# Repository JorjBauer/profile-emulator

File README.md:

# ProFile emulator

This is a replacement for an Apple ProFile hard drive. It plugs into the cable
from an Apple ][ ProFile interface card, answers the card the way a real
ProFile does, and serves blocks from disk images on a microSD card.

## How it got here

In 2021 I built a reader for my ProFile 10 around a Teensy 4.1, so I could get
the drive's contents into a disk image. That's
[profile-dumper](https://github.com/JorjBauer/profile-dumper), and the build
log is on [Hackaday](https://hackaday.io/project/179930-apple-profile-10mb-hard-drive-reader).

At the same time, I hand-wired a second Teensy board meant to turn that around
and pretend to be the drive instead of the host. Its code wasn't finished
until 2026. That's the Teensy version in `teensy/`, and it works on my //e.
But it's at the limit of what the Teensy can do, and it took some clever
optimization to get there.

So I moved it to an FPGA. I chose to make it FPGA-only, with no
microcontroller, to keep the cost down. That drove the complexity up. I started
on an Alchitry Cu (iCE40 HX), moved to the Alchitry Au (Artix-7) when the
iCE40's carry chains became the bottleneck, and then moved to a ULX3S-12F
(ECP5). If you find comments about the iCE40 or the Artix-7, that's why.

Then I built two boards of my own around the same ECP5 in a TQFP-144. r1
worked after some rework, but it had the wrong footprint for the flash chip,
along with other mistakes. r2 fixed them, and it's been serving my //e since
2026-10-23.

All of my testing is on a //e with a ProFile card whose ROM is 341-0299-B. I
haven't tried an Apple ///.

## What's here

- `fpga/`: the current design. Its `README.md` is the technical notebook:
  architecture, the serial report, the boot menu, and the tests.
  - `src/` and `sim/`: the Verilog and its testbenches.
  - `constraints/`: pinouts for the ULX3S (`ulx3s.lpf`) and r2
    (`profile-drive-r2.lpf`).
  - `tools/`: node scripts. One imports the selector's blobs into the build;
    the others check a card image against what the drive serves.
  - `carrier/ULX3S-ADAPTER.md`: wiring the interface board to a ULX3S.
  - `hw-r2/profile-drive/`: the r2 board. The KiCad project, the Gerber and
    stencil zips, a placement sheet and an assembly drawing.
  - `hw-r2/BRINGUP-r2.md`: building an r2 board and bringing it up.
  - `hw-r2/enclosure/`: a printed case shaped like a tiny ProFile.
- `teensy/`: the Teensy 4.1 version. It still works.
- `selector/`: a submodule with the 6502 boot menu that both versions serve,
  so you can pick an image from the //e.

The ProFile protocol, the DB-25 pinout and the interface card's behavior are
documented in profile-dumper's `PROTOCOL.md` and `HARDWARE.md`. The READMEs
here refer to them often.

## Getting the code

The selector is a submodule, so clone with it:

    git clone --recursive <this repo>

If you already cloned without it, run `git submodule update --init`.

## Where to start

### Preparing an SD card

Format it FAT32, put your images in a directory named `HD`, and create
`/profile.cfg` by hand with any non-empty content. The drive can rewrite
files, but it can't create them. The details are in `fpga/README.md` under
"Preparing the SD card".

### Building for a ULX3S

You need [oss-cad-suite](https://github.com/YosysHQ/oss-cad-suite-build),
which has yosys, nextpnr-ecp5, ecppack, iverilog, openFPGALoader and fujprog.
You also need `node`, because the build uses it to import the selector's
blobs. Then, in `fpga/`:

    make sim-all    run the testbenches
    make            build the bitstream
    make prog       load it into SRAM, volatile
    make flash      write it to the SPI flash

`make sim-all` stops at the first bench that fails. `fpga/README.md` has the
full list of targets.

The ULX3S needs an interface board between it and the DB-25: two 74LVC245s
that shift the 5V bus down to 3.3V. Mine was hand-wired on perfboard, and its
design isn't in this repo. `fpga/carrier/ULX3S-ADAPTER.md` has the pin map
from that board to the ULX3S, and the wiring mistakes that damage parts.

### Ordering r2 boards

Everything is in `fpga/hw-r2/profile-drive/`.

- `profile-drive-r2-gerbers.zip` is the board: 4 layers, 1.6 mm, lead-free
  HASL, 1 oz outer copper, 100 x 55 mm.
- `profile-drive-r2-stencil-reduced.zip` is a top paste layer with the
  apertures on U1 and J1 shrunk by 0.04 mm. The full-size paste in the Gerber
  zip bridged their fine-pitch pins on my board. I ordered it in 4 mil
  stainless.
- Every part is on the top side.
- The silkscreen labels are 0.8 mm tall. That's below JLCPCB's standard 1.0 mm
  minimum, and at their limit for high-precision silkscreen (0.8 mm text with
  a 0.1 mm stroke), so ask for high-precision if you want the smallest labels
  crisp.

If you want JLCPCB to assemble it, upload these two as well:

- `profile-drive-r2-bom-jlcpcb.csv`: the BOM, with the manufacturer part and
  the LCSC number for each line. Every LCSC number is the exact part in the
  schematic, except for the LEDs, which the schematic doesn't name. The BOM
  uses red ones (KENTO KT-0603R).
- `profile-drive-r2-cpl-jlcpcb.csv`: the pick-and-place file, in the same
  coordinates as the Gerbers. I haven't had JLCPCB assemble one, so check
  every part's rotation in their preview before you pay. The TQFP, the
  SOT-23s, the TSSOPs and the connectors are the usual suspects.

J4, J5, J6, J7 and SW1 are optional and left out of both files. They're for
programming, debugging and service, and you can solder them on later. A new
board's flash is blank, though, so something has to reach J4's pads once to
load it. I use a pogo-pin clip on J4. A 1x6 header soldered there works too.

As of 2026-10-24, three parts had no stock at JLCPCB: U1 (the FPGA), J1 (the
USB-C socket) and J2 (the DB-25). You'll probably have to send those in
yourself or solder them by hand. R31 (84.5k) had only 17 in stock.

The LCSC numbers are also in the schematic, as an `LCSC` field on each part,
and J4, J5, J6, J7 and SW1 are marked DNP in both the schematic and the board. If
you change the design, KiCad's own BOM and position exports pick both up, but
the two CSV files here won't follow on their own.

### The LEDs

The schematic gives each of the eight LEDs a 1k resistor (R35 to R42, in
order for D1 to D8) and doesn't name a color. That's sized for ordinary red or
yellow 0603 LEDs. The BOM uses red (KENTO KT-0603R, LCSC C2286). For yellow,
NationStar NCD0603Y2 (LCSC C89811) works the same way.

The LEDs and their resistors are optional. Nothing else is on those nets, so
leaving them off only loses the status display and the error codes.

If you use white, blue or true green LEDs, change their resistors to 330R.
Those colors need about 3 V to light, which leaves only a few tenths of a volt
across the resistor from a 3.3 V pin, so at 1k they're dim. On my board D1 to
D4 matter most, so D1 is white, D2 is blue, D3 and D4 are emerald, and R35 to
R38 are 330R.

### Building one by hand

`placement-r2.png` is the assembly sheet. It shows where each part
goes, marks pin 1 (and each LED's cathode) in red, and has a checklist BOM with
quantities and part numbers. `assembly-r2.pdf` puts the values on the
footprints. Use the reduced stencil.

`fpga/hw-r2/BRINGUP-r2.md` walks through the rest: paste and reflow,
inspection, checking the power rails, first power, and programming.

### Updating an r2 board

The flash holds two copies of the gateware: the one that runs, and a golden
copy the board falls back to if the first is ever damaged. A new board gets
both over JTAG, once. After that, an update can come from the SD card.

In `fpga/`, `make r2-flash-dual` builds the gateware and writes both copies,
plus the record that points the FPGA at the golden one. The programmer is an
FT4232H module on J4, through a pogo-pin clip or a header soldered there. The
wiring is in `fpga/README.md` under "Building for the r2 board". Power the
board from USB-C, not from J4. (`make r2-prog` loads SRAM instead, for
testing.)

For an update from the SD card, `make r2-update` builds `R2UPDATE.BIN`. Copy
it to the root of the card and power the board up. It waits until the drive
is idle, so it never slows a boot. If the file holds a newer build than the
one running, the LEDs fill up twice (once checking the file, once writing
it) while the drive keeps serving. After five seconds with no activity from
the //e, the board reboots into the new build. The file can stay on the
card; it's skipped once it's the build that's running, and an older file is
always skipped. Going back to an older build takes JTAG. `fpga/README.md`
has the details under "Updating from the SD card".

To check which build a board is running, hold open-apple while the //e
boots, and the image menu comes up. Row 2 shows the build ID and which copy
it was loaded from, such as `BUILD 80068B67 (PRIMARY)`. Build IDs only go
up, so a higher one is newer. It says `GOLDEN` if the first copy was damaged
and the board fell back. The bottom row shows what each copy in the flash
holds, which only differs from row 2 when an update is waiting for its
reboot. (The menu needs at least one image on the card.)

There are no prebuilt bitstreams yet, so you need the same tools as the ULX3S
build.

### The Teensy version

`teensy/README.md` covers the wiring, the arduino-cli build and the serial
commands. The board was hand-wired, so its README is an as-built description,
not a schematic.

## What doesn't work yet

- The SD card update passes its simulations, but I haven't tried it on a
  board yet. Neither the fallback to the golden copy nor the reboot at the
  end has been seen working on real hardware. JTAG works.
- No prebuilt bitstreams.
- The ULX3S interface board's design isn't published.
- Nobody has tried it on an Apple ///.

## License

MIT. See `LICENSE`.

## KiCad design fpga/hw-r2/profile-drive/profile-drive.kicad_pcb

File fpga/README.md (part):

# ProFile emulator in an FPGA

This is the FPGA version of the drive. It answers the ProFile's DB-25
protocol and serves blocks from an SD card, on a ULX3S or on the r2 board in
`hw-r2/`. The top-level README has the backstory and says where to start; this
is the technical notebook.

`PROTOCOL.md` and `HARDWARE.md` below are the ones in
[profile-dumper](https://github.com/JorjBauer/profile-dumper).

## Preparing the SD card: a file you have to create yourself

Format the card FAT32, put your images in a directory called `HD`, and
then **create `/profile.cfg` in the root of the card by hand**, with
any text editor and any non-zero-length content, so the drive can
remember its state.

**This drive can modify files, but it cannot create them.** Every
write it performs must be in a sector that is already allocated: a
host's write goes into the image's own cluster chain, and remembering
a menu selection rewrites `profile.cfg`'s existing data sector and
then corrects the size in its directory entry. There is no allocator,
no free-cluster search and no FAT writing anywhere in it, because
serving a fixed-size volume never needs one. Only creating a file
would need them. A text file you drop on the card
avoids all that complexity.

The images must be in a directory named `HD` as a practical matter;
the more stuff the descender has to enumerate, the longer it takes for
this device to boot. We have about 0.58s before the Apple ][ ProFile card
ROM gives up; unlike some other cards, it makes one STATUS request and then
bails if it doesn't respond.

## Building it

This builds with an open source toolchain: yosys, nextpnr-ecp5, and
prjtrellis, all of which are part of oss-cad-suite. The build also needs
`node`, which imports the selector's blobs. Source oss-cad-suite's
environment first (`source <wherever you unpacked it>/environment`) and then

    make            synthesize, place and route, pack
    make sim-all    the testbenches. Run these before touching hardware
    make prog       load into SRAM over USB, volatile
    make flash      write SPI flash, survives a power cycle
    make reload     re-load the last SRAM build with no rebuild
    make stat       resource count only: yosys alone, no place and route
    make clean

`make stat` needs nothing but yosys, which makes it the fastest way to see
whether a change still fits.

**SRAM and flash get different bitstreams.** The flash copy is
compressed and configured for fast-read at 38.8 MHz (62 MHz on r2). An
uncompressed stream takes about 2.25 s to load and loses the power-on
race against the //e. Compressed, the same load is about 70 ms.
Loading that same compressed flavor into SRAM over JTAG makes the
ECP5's config engine abort with `BSE Abort ERR` and leaves the device
blank. `make prog` therefore builds and loads the uncompressed
`_nextflash.bit`, and `make flash` the compressed one. Both work via
`fujprog`.

There is one more ECP5 wrinkle worth knowing: this is built as an
ECP5-25F, but I'm using an ECP5-12F to serve it. They're the same
silicon; the 12F has artificial limits that the open source toolchain
is happy to ignore.

Four separate diagnostic bitstreams build from the same sources, each
of which takes the SD engine or the bus for itself and so cannot
coexist with serving a host: `make verify-prog` (whole-volume
checksums), `make dump-prog DLBA=n` (one sector as hex), `make
exercise-prog` (a known pattern on the DB-25 with no host) and `make
stream-prog SBLOCK=n` (a real block onto the DB-25 with no host). Each
is described in its own section below.

### Building for the r2 board

The r2 board in `hw-r2/` is this same design on an LFE5U-12F in a
TQFP-144, with its own pinout in `constraints/profile-drive-r2.lpf`. r2 has
three pins the ULX3S build doesn't, so its top module is `src/top_r2.v`,
which wraps `top` and leaves every other build alone:

- **U3_OE_N** (pin 76) enables U3, the buffer for the host's control lines.
  R53 holds it off until the FPGA is configured, and the gateware ties it low.
  If it isn't driven low, the FPGA never sees /PCMD or /PSTRB.
- **XCVR_OE_N** (pin 74) is held off until the host asserts /PCMD the first
  time, because PD0 to PD7 have no pulls and float with no cable.
- **FPGA_REBOOT** (pin 67) goes to PROGRAMN through R48. The SD update pulls
  it low through an explicit open-drain pad when it's done, and otherwise it's
  released. Don't make it an output assigned `1'bz`: nextpnr turns that into a
  driven pin, and low there reboots the part over and over. It must never be
  driven high either.
- **The flash** (pins 46, 47 and 49, and the configuration clock through
  `USRMCLK`) is ours once the part is configured. The SD update uses it.

It builds next to the ULX3S flavor under its own name:

    make r2             both bitstreams
    make r2-prog        load SRAM over JTAG, volatile
    make r2-reload      the same with no rebuild
    make r2-flash-dual  write both flash images and the jump record over JTAG
    make r2-flash       rewrite just the primary image over JTAG
    make r2-update      build R2UPDATE.BIN, for an update from the SD card

JTAG is an FT4232H module on J4, channel A, under the module's UART
labels: TXD to TCK (J4 pin 4), RXD to TDI (pin 3), RTS to TDO (pin 2),
CTS to TMS (pin 5), GND to pin 6, nothing on pin 1. `R2CABLE=` overrides
the cable name. Power the board from USB-C, not from J4.

After any rebuild, read the catalog back (the dumper's `K`, or a window
read of `$FFFF80`) rather than trusting the boot alone. A build can meet
timing and pass every simulation and still serve a wrong catalog (see the
fat32 note under "Known bring-up items").

The first r2 build lost the power-on race on a
cold start. The //e's card ROM looks for the drive about 0.6 s after
autostart reaches the slot, and if /PBSY or PCHK is wrong it skips the slot
and never asks again. Two things changed, both only for r2:

- The FPGA reads its flash at 62 MHz (`FLASHFREQ`, ecppack's top rate)
  instead of 38.8. The 348 KB compressed load drops from about 72 ms to
  about 45. The W25Q128 is good to 133 MHz.
- The SD card initializes at 397 kHz (`SD_DIV_INIT` 62) instead of 100 kHz.
  That's just under the 400 kHz the SD spec allows for initialization, and
  it's fine now that the socket is on the board rather than on flying leads.
  The first read also happens at this rate, so it's faster too.

After that, reads and writes both run at 8.33 MHz. The ULX3S harness kept
writes at 391 kHz, but the first r2 board passed every rate up to 25 MHz
(see "Measuring an r2 board's SD clock ceilings"), so r2 writes at the read
rate. 8.33 MHz is a third of what the board was shown to do.

The FAT32 directory recursion is still on. It costs boot time when the card
holds a lot of files, which is why the images belong in `HD`.

With both changes, build 10231827 (60.17 MHz against the 50 MHz target)
serves the //e from a cold start. I couldn't measure how much margin is
left. The //e's monitor takes longer to come up than the drive does, so
there's nothing to time on the screen.

## Updating from the SD card

r2 can rewrite its own flash from a file on the SD card and reboot into it.
`src/fw_update.v` does the work, through `src/spi_flash.v`. It's only built
into r2 (`UPDATE_ENABLE`), since the ULX3S has no line from the FPGA to
PROGRAMN.

### The flash layout

    0x000000   the primary image: 256 bytes of $FF, then the bitstream
    0x100000   the golden image, laid out the same way
    0xFFFF00   a jump record pointing at the golden image

The updater only ever writes below 0x100000. If the primary fails to
configure, because an update lost power partway through for instance, the
ECP5 follows the jump record to the golden copy at power-up (Lattice
FPGA-TN-02203). The golden copy carries the updater too, so it finds the file
again and finishes the job. `make r2-flash-dual` writes all three pieces over
JTAG, which a board needs once.

The layout is ecpmulti's, but we don't use ecpmulti. It re-serializes every
bitstream and drops `--compress`, `--freq` and `--spimode`, and r2 needs all
three to win the power-on race. `ecppack --bootaddr` sets multiboot instead,
and `tools/mkupdate.js` writes the jump record. Both images point their next
boot at 0. ecpmulti points the primary at the golden copy instead, and then
the reboot after an update would land on the golden copy, which would write
the same file again and reboot again, forever.

### The file

`make r2-update` builds `R2UPDATE.BIN`: a 512-byte header, then the primary
image padded to whole sectors. The header holds `PEFW`, the board (`R2`), the
payload's length, its CRC-32 and its `BUILD_ID`. Put it in the root of the
card.

### Which build is where

There's no separate version number. The `BUILD_ID` does the job: it's the
minutes since 2026-01-01 00:00 UTC with the top bit set, so it only goes up,
and a higher one is always a newer build. The build puts it in the gateware
and in the bitstream's header as a comment, `PEV:<BUILD_ID>`, ahead of
nextpnr's own. The header comes right after a slot's 256 bytes of $FF, so the
comment always starts 258 bytes into the slot.

At reset, before anything else, the updater reads both slots' headers. That
takes about 30 microseconds and doesn't touch the SD card. Whichever slot
carries the running `BUILD_ID` is the one we were loaded from. If neither
does, the gateware came in over JTAG. A slot can also read `EMPTY` (erased),
or `UNKNOWN` (no build ID in its header). Headers written by builds from
before this change say `PEV:<BUILD_ID>:1.0`, and the updater reads the build
ID out of those too. After an update writes the primary, it reads the
primary's header again, so the menu shows what's waiting for the reboot.

The select menu shows all of it, from the info block (`selector/SELECTOR.md`
has the layout):

    BUILD 80068B67 (PRIMARY)            row 2: what's running, and its slot
    PRIMARY 80068B67  GOLDEN 80068B38   bottom row: what each slot holds

The ULX3S shows only the first line, without a slot. The Teensy shows neither.

Whether the primary matches is all the slot test checks. If the primary's
header survives but the rest of it is damaged, the ECP5 loads the golden
copy instead, and if the two copies are the same build, the menu still says
`PRIMARY`. In that case it's the same gateware either way.

### What happens at power-up

Boot time comes first, so the updater does nothing until the drive is idle:
a full second with no host command, no block reads or writes, and the SD
card at rest. A booting //e reads with gaps of a few milliseconds, so the
updater never touches the card during a boot. Then it looks for
`R2UPDATE.BIN` in the root, which takes a few sector reads. It stops there
if:

- there's no file
- the file's `BUILD_ID` isn't newer than the one that's running. That's
  what keeps an update from repeating, so the file can stay on the card, and
  it means an older file is ignored. Going back to an older build takes
  JTAG (`make r2-flash-dual`).

Otherwise it makes two passes, in the background. The drive keeps serving
the whole time: the updater is the SD card's lowest-priority user, so a host
read waits at most for the one updater read already in flight (well under a
millisecond). The first pass reads the whole file and checks its CRC, and
writes nothing. The second erases each 64 KB block as it reaches it,
programs each sector, and reads it back. An update of the current 371 KB
image reads the card twice and writes about 6 blocks, which takes a few
seconds.

Then it waits for the drive to be idle again, and to stay idle for four
more seconds (five in all), before it pulls PROGRAMN. That reboot is the
only part a host can notice: the drive is gone while the FPGA configures and
mounts the card again, the same wait as at power-up. If the //e is in the middle of something
then, it gets an error. If the host never goes quiet for five seconds, the
board keeps running the old image, and the new one starts at the next
power-up.

The LEDs show it. During the first pass they fill from D1 to D8, blinking.
During the second they fill again, solid. All eight stay lit while it waits
to reboot. A failure blinks D8 and shows the error code on D1 to D4 (D1 is bit
0), until a host appears:

| code | meaning |
|-----:|---------|
| 1 | an SD read failed |
| 2 | the header isn't `PEFW`, or its length is bad |
| 3 | the file is for another board |
| 4 | the payload doesn't match its CRC |
| 5 | the file ends before its payload does |
| 6 | the flash didn't answer as a W25Q128 |
| 7 | an erase timed out |
| 8 | a page program timed out |
| 9 | a sector read back differently |

Errors 2 to 6 happen before anything is written, and so can error 1. Errors 7 to 9, and an error 1 during
the second pass, leave the primary half written. The running image is
fine until power is removed, and at the next power-up the board falls back
to the golden copy, which tries again.

The serial report carries the same status in the `FAT` line, words 4 to 6,
when the self-test's FAT scan isn't built in: `[25:24]` the pass (1 check, 2
write, 3 done), `[19:16]` the error, `[15:0]` the sectors done; then the
sectors in all; then the file's `BUILD_ID`.

`make sim-fw-update` runs it against a hand-built FAT32 card and a model
flash. A good file is written and read back, with its directory entry and
its clusters both scattered so the FAT has to be followed. A file that's
already running, corrupted, built for another board, missing, or that reads
back wrong is refused. Nothing at or above the golden image is ever written.
It doesn't start until the drive is idle, and host activity holds the reboot
off until the drive has been idle long enough.

**None of this has run on a board yet.** The simulation covers the updater's
own logic. It can't show that the ECP5 really falls back to the golden copy,
that `USRMCLK` drives the flash clock as expected, or that the reboot works.
Before trusting it, flash a board with `make r2-flash-dual`, then try an
update. Then erase the first block of the flash over JTAG and power-cycle the
board, to check it comes up from the golden copy.

One case can still loop. If a file passes every check but its image won't
configure, the board falls back to the golden copy, which writes the same
file again, and reboots into it. Each round takes a few seconds, and the
LEDs show it happening. Taking the card out stops it.

## Electrical: the bus is 5V, the FPGA is not

Two 74LVC245s serve as voltage level converters, since the FPGAs are
not 5v tolerant and the ProFile bus is 5V TTL.

## Architecture

    db25 <-> 74LVC245 pair <-> profile_bus (tri-state, parity)
                                    |
                              profile_target      the three-phase protocol FSM
                                    |
                        +-----------+-----------+
                        |                       |
                  block_router            status/geometry
                  (normal blocks,        (spare table for $FFFFFF,
                   $FFFFFE RAM buf,       4 status bytes, the
                   selector magic)        multiple-of-4 rule)
                        |
                +-------+-------+
                |               |
             fat32           selector      the image menu's drive half
        (MBR, BPB, the      ($FFFF00..
         directory walk,     $FFFFFD)
         cluster chains,
         profile.cfg)
                |
             sd_spi  ->  SD card  (SPI mode, CMD17/CMD24)

`reporter` streams the whole diagnostic state out the serial port (the
ULX3S's USB serial, or J5 on r2); it is not in the data path.

Module by module:

- **`profile_bus`** owns the pins: tri-state control, the `DIR`//`OE` pair for
  the translators, and odd parity. Parity is generated for **host-driven bytes
  too**, including the ack (`PROTOCOL.md` §9.4): the drive owns that line in
  both directions. Getting it wrong is what makes a parity latch appear to set
  itself.
- **`profile_target`** implements command / confirmation / data phases, the six
  command bytes, the `$55` ack and the `$AA` NAK, and the //e's two departures
  from the spec: a read is 4 status + 512 with the host then abandoning by
  re-asserting `/PCMD`, and a write is 512 + a 6-byte trailer
  (`PROTOCOL.md` §3 and §9.1, §9.3).
- **`block_router`** decodes the 24-bit block number: normal blocks to the SD
  reader, `$FFFFFE` to the RAM buffer, `$FFFFFF` to the synthesized spare table,
  and the `$FFFF00-$FFFFFD` selector window.
- **`sd_spi`** is a plain SPI block reader: init at 100 kHz (397 kHz on r2),
  run at the measured rates in the table below, CMD17 single-block read and CMD24 write. **Both
  card generations work.** SDHC addresses by block; a card that rejects CMD8 is
  treated as v1, ACMD41 goes out without HCS, CCS comes from the OCR, and CMD17
  arguments are scaled by 512. `make sim-v1` and `make sim-v1skew` are that
  path. It also recovers byte alignment when a card's replies arrive out of
  phase, which the real one does: `make sim-sweep` checks the recovery over all
  eight bit phases.

## Geometry, and what reverse engineering revealed

The claimed volume size in the spare table **must be a multiple of 4**
or the //e's ROM never hands off to the boot block (`PROTOCOL.md`
§9.2). The drive rounds down and caps the claim at `$FFFC`, which is
what the Teensy firmware does, and it will not be configured
otherwise. It is one comparator and it prevents an entire class of "it
reads fine but will not boot". Also see "Geometry: two block counts,
not one" below.

## Testing against the //e, not just the reader

`make sim` runs the protocol against a model of the READER's host
sequence, which is deliberately forgiving: microseconds per byte, a
settling delay after `PR/-W` rises, generous strobes. A drive that
fails there cannot possibly work. Passing it shows very little, and
PROTOCOL.md section 3 says so: the Apple /// and Lisa hosts insert
a delay before their first strobe, "which is why a slow drive works
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
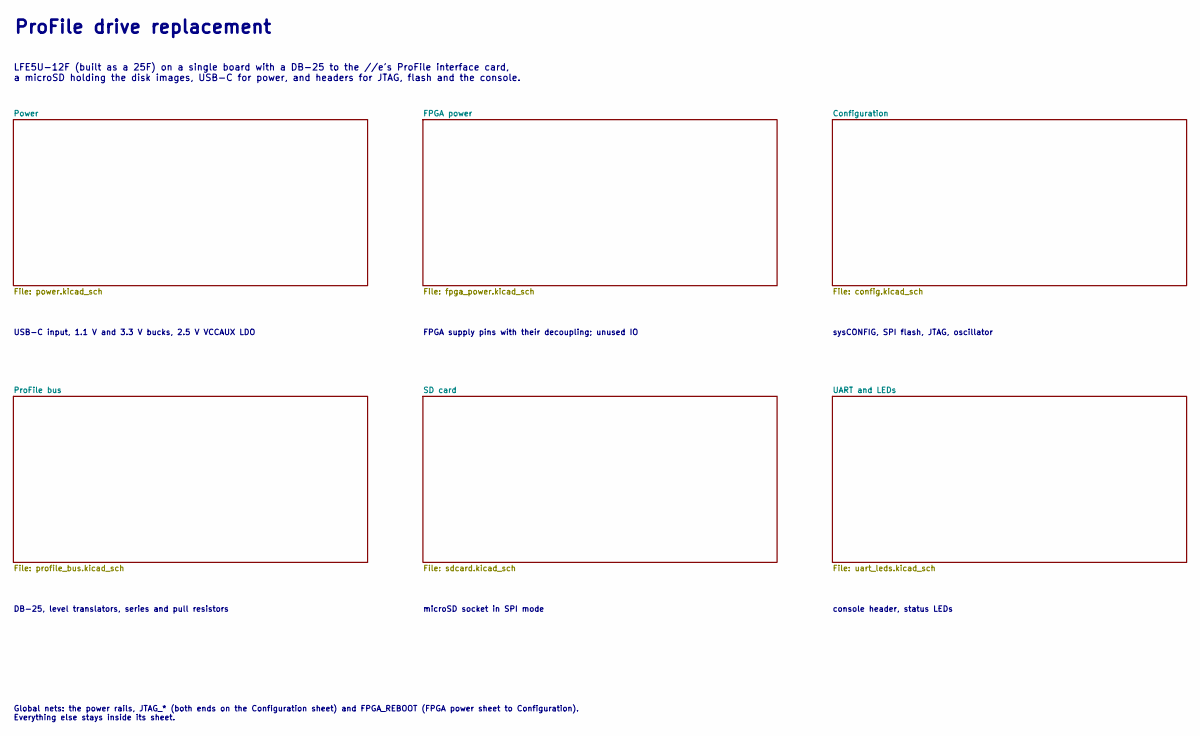
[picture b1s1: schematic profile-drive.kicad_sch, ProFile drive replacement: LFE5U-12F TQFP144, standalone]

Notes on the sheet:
ProFile drive replacement
LFE5U-12F (built as a 25F) on a single board with a DB-25 to the //e's ProFile interface card, a microSD holding the disk images, USB-C for power, and headers for JTAG, flash and the console.
USB-C input, 1.1 V and 3.3 V bucks, 2.5 V VCCAUX LDO
FPGA supply pins with their decoupling; unused IO
sysCONFIG, SPI flash, JTAG, oscillator
DB-25, level translators, series and pull resistors
microSD socket in SPI mode
console header, status LEDs
Global nets: the power rails, JTAG_* (both ends on the Configuration sheet) and FPGA_REBOOT (FPGA power sheet to Configuration). Everything else stays inside its sheet.

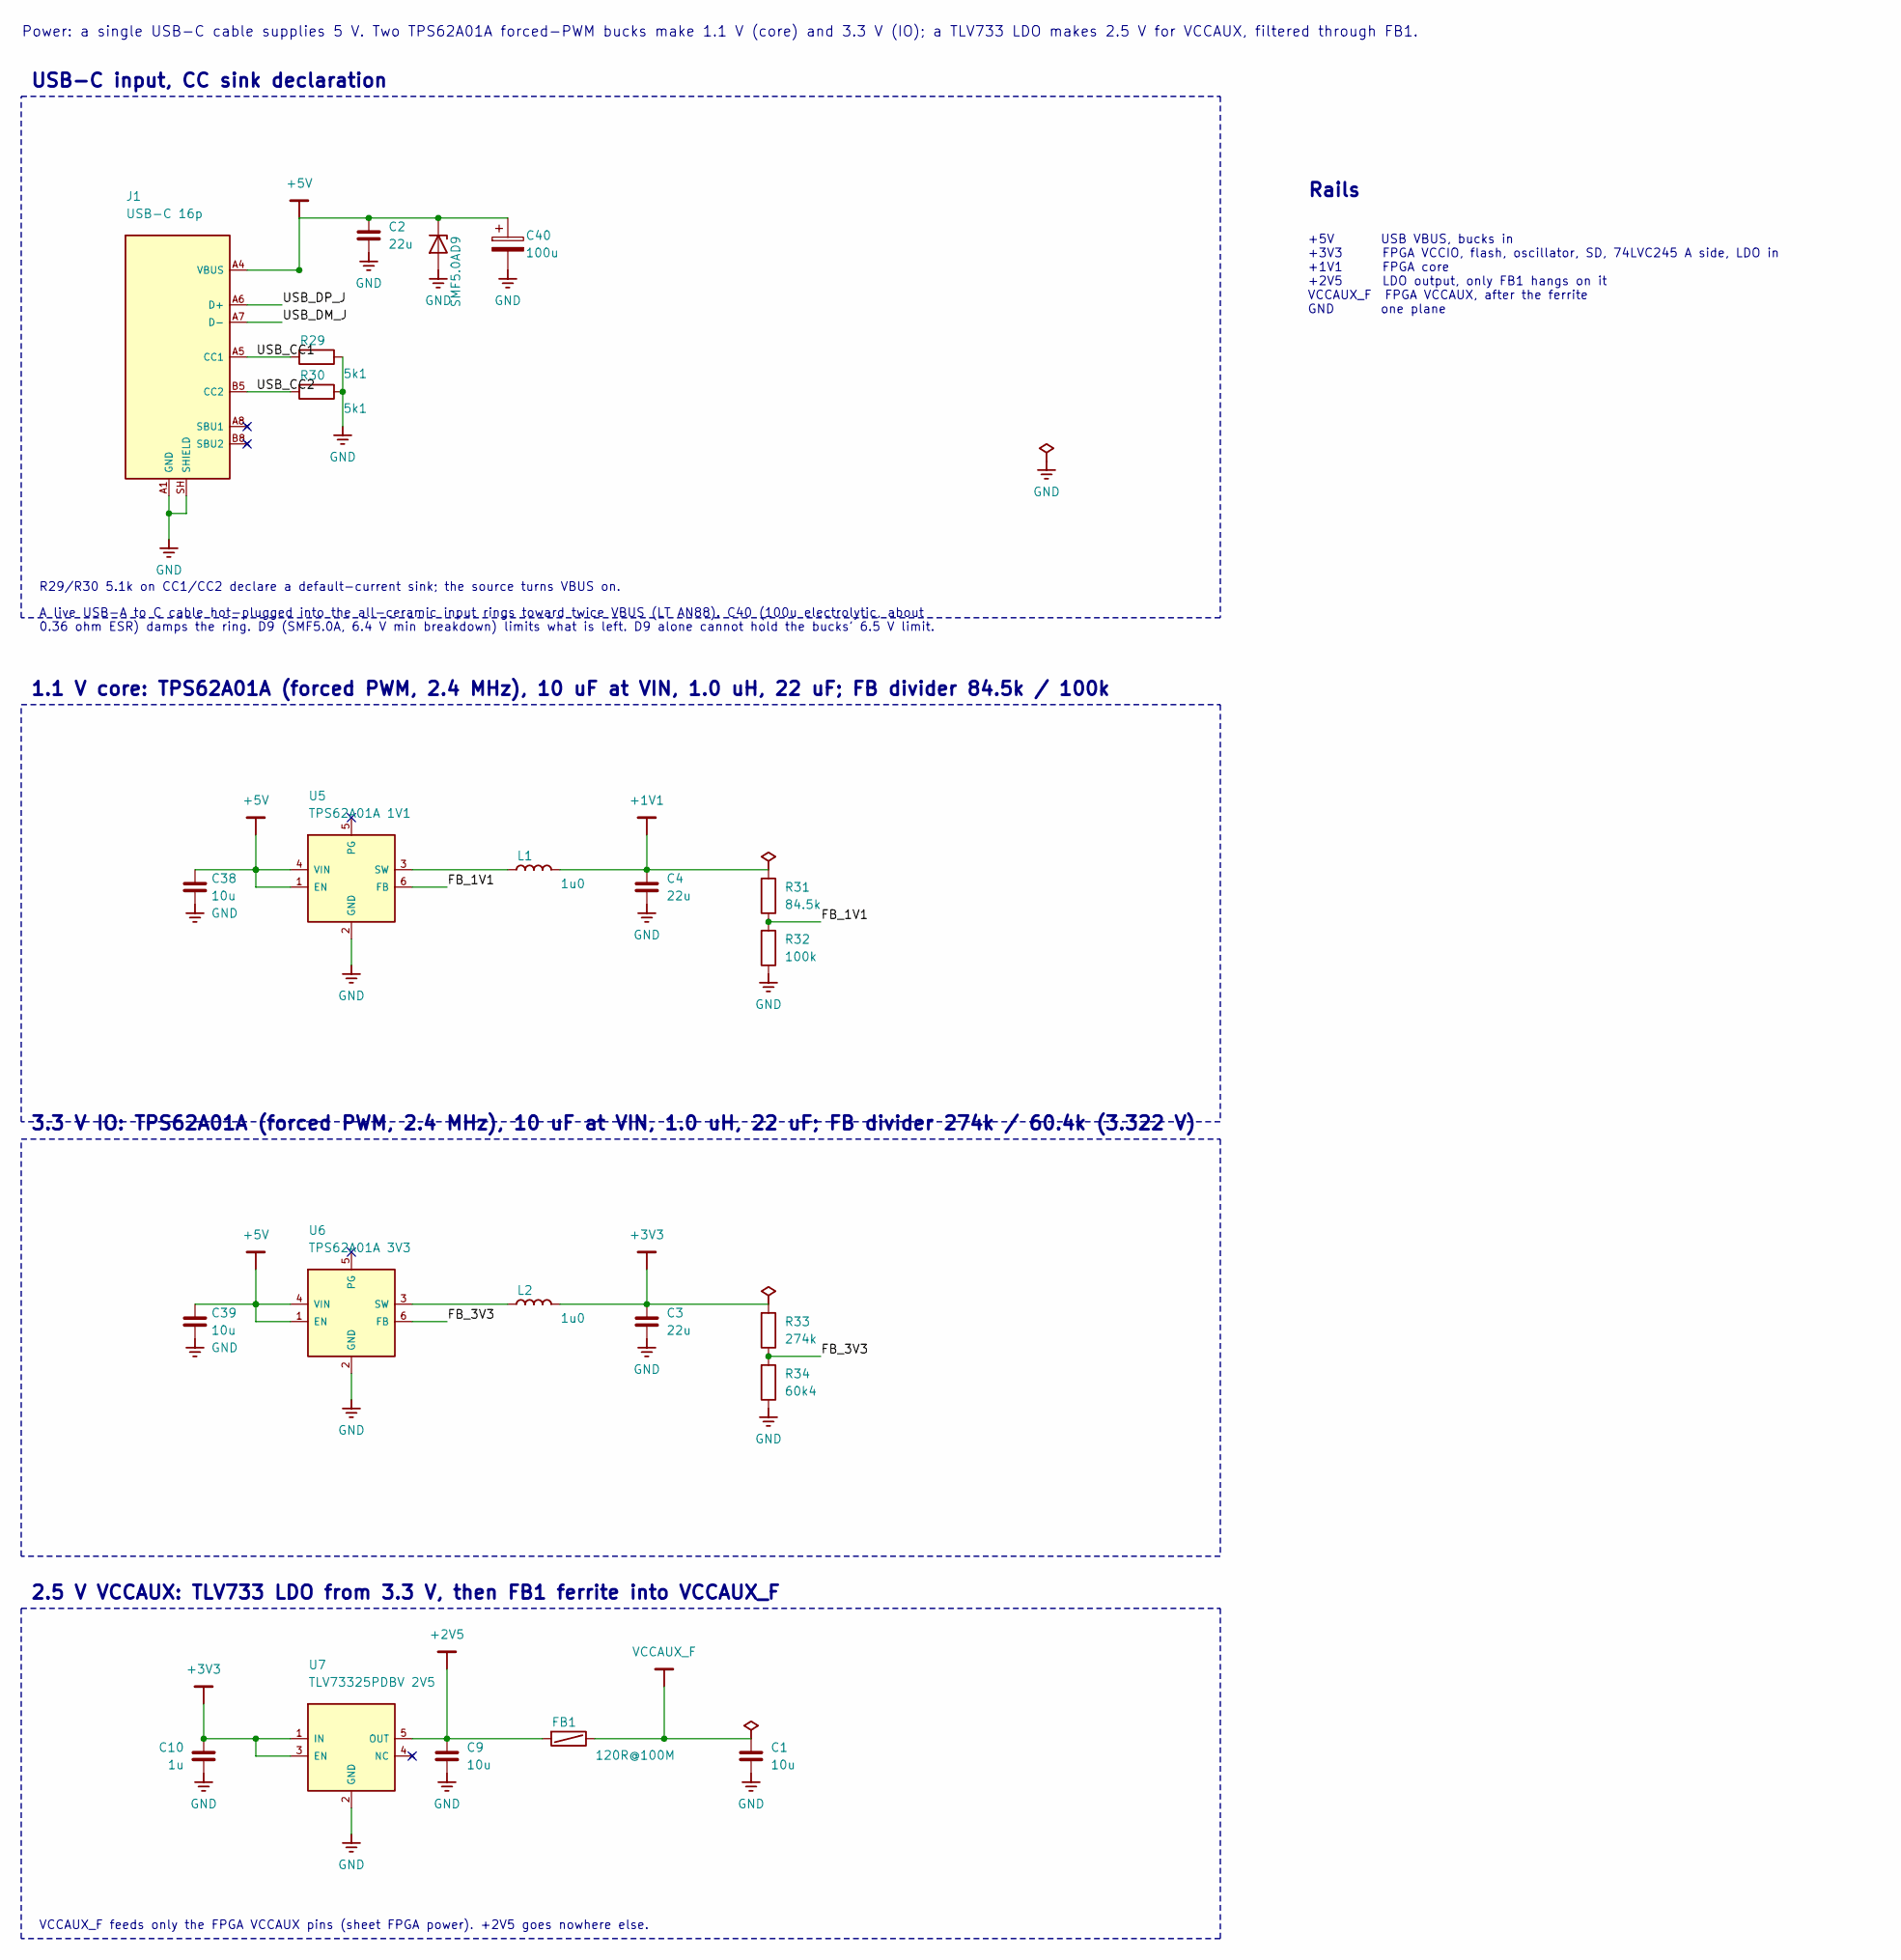
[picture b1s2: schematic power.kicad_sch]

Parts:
C1, C9, C38, C39: 10u; C_0603_1608Metric; MPN Murata GRM188R61E106MA73D; LCSC C91606
C2, C3, C4: 22u; C_1206_3216Metric; MPN Samsung CL31A226KAHNNNE; LCSC C12891
C10: 1u; C_0603_1608Metric; MPN Samsung CL10B105KA8NNNC; LCSC C29936
C40: 100u; CP_Elec_6.3x5.8; MPN Panasonic EEE-FK1C101P; LCSC C128532
D9: SMF5.0A; D_SOD-123F; MPN Littelfuse SMF5.0A; LCSC C151296
FB1: 120R@100M; L_0603_1608Metric; MPN Murata BLM18PG121SN1D; LCSC C14709
J1: USB-C 16p; USB_C_Receptacle_GCT_USB4105-xx-A_16P_TopMnt_Horizontal; MPN GCT USB4105-GF-A; LCSC C3020560
L1, L2: 1u0; L_Murata_DFE252012F; MPN Murata DFE252012F-1R0M=P2; LCSC C435392
R29, R30: 5k1; R_0603_1608Metric; MPN Yageo RC0603FR-075K1L; LCSC C105580
R31: 84.5k; R_0603_1608Metric; MPN Yageo RC0603FR-0784K5L; LCSC C326920
R32: 100k; R_0603_1608Metric; MPN Yageo RC0603FR-07100KL; LCSC C14675
R33: 274k; R_0603_1608Metric; MPN Yageo RC0603FR-07274KL; LCSC C482818
R34: 60k4; R_0603_1608Metric; MPN Yageo RC0603FR-0760K4L; LCSC C165742
U5: TPS62A01A 1V1; SOT-23-6_Handsoldering; MPN TI TPS62A01APDDCR; LCSC C41730179
U6: TPS62A01A 3V3; SOT-23-6_Handsoldering; MPN TI TPS62A01APDDCR; LCSC C41730179
U7: TLV73325PDBV 2V5; SOT-23-5_HandSoldering; MPN TI TLV73325PDBVR; LCSC C882825

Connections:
+1V1: C4.1, L1.2, R31.1; also elsewhere on the board
+2V5: C9.1, FB1.1, U7.5 (OUT)
+5V: C2.1, C38.1, C39.1, C40.1, D9.1 (K), J1.A4 (VBUS), J1.A9 (VBUS), J1.B4 (VBUS), J1.B9 (VBUS), U5.1 (EN), U5.4 (VIN), U6.1 (EN), U6.4 (VIN)
/Power/FB_1V1: R31.2, R32.1, U5.6 (FB)
/Power/FB_3V3: R33.2, R34.1, U6.6 (FB)
/Power/USB_CC1: J1.A5 (CC1), R29.1
/Power/USB_CC2: J1.B5 (CC2), R30.1
/Power/USB_DM_J: J1.A7 (D-), J1.B7 (D-)
/Power/USB_DP_J: J1.A6 (D+), J1.B6 (D+)
unnamed: L1.1, U5.3 (SW)
unnamed: L2.1, U6.3 (SW)
VCCAUX_F: C1.1, FB1.2; also elsewhere on the board

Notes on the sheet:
Power: a single USB-C cable supplies 5 V. Two TPS62A01A forced-PWM bucks make 1.1 V (core) and 3.3 V (IO); a TLV733 LDO makes 2.5 V for VCCAUX, filtered through FB1.
USB-C input, CC sink declaration
R29/R30 5.1k on CC1/CC2 declare a default-current sink; the source turns VBUS on.
1.1 V core: TPS62A01A (forced PWM, 2.4 MHz), 10 uF at VIN, 1.0 uH, 22 uF; FB divider 84.5k / 100k
3.3 V IO: TPS62A01A (forced PWM, 2.4 MHz), 10 uF at VIN, 1.0 uH, 22 uF; FB divider 274k / 60.4k (3.322 V)
2.5 V VCCAUX: TLV733 LDO from 3.3 V, then FB1 ferrite into VCCAUX_F
VCCAUX_F feeds only the FPGA VCCAUX pins (sheet FPGA power). +2V5 goes nowhere else.
Rails
+5V USB VBUS, bucks in +3V3 FPGA VCCIO, flash, oscillator, SD, 74LVC245 A side, LDO in +1V1 FPGA core +2V5 LDO output, only FB1 hangs on it VCCAUX_F FPGA VCCAUX, after the ferrite GND one plane
A live USB-A to C cable hot-plugged into the all-ceramic input rings toward twice VBUS (LT AN88). C40 (100u electrolytic, about 0.36 ohm ESR) damps the ring. D9 (SMF5.0A, 6.4 V min breakdown) limits what is left. D9 alone cannot hold the bucks' 6.5 V limit.

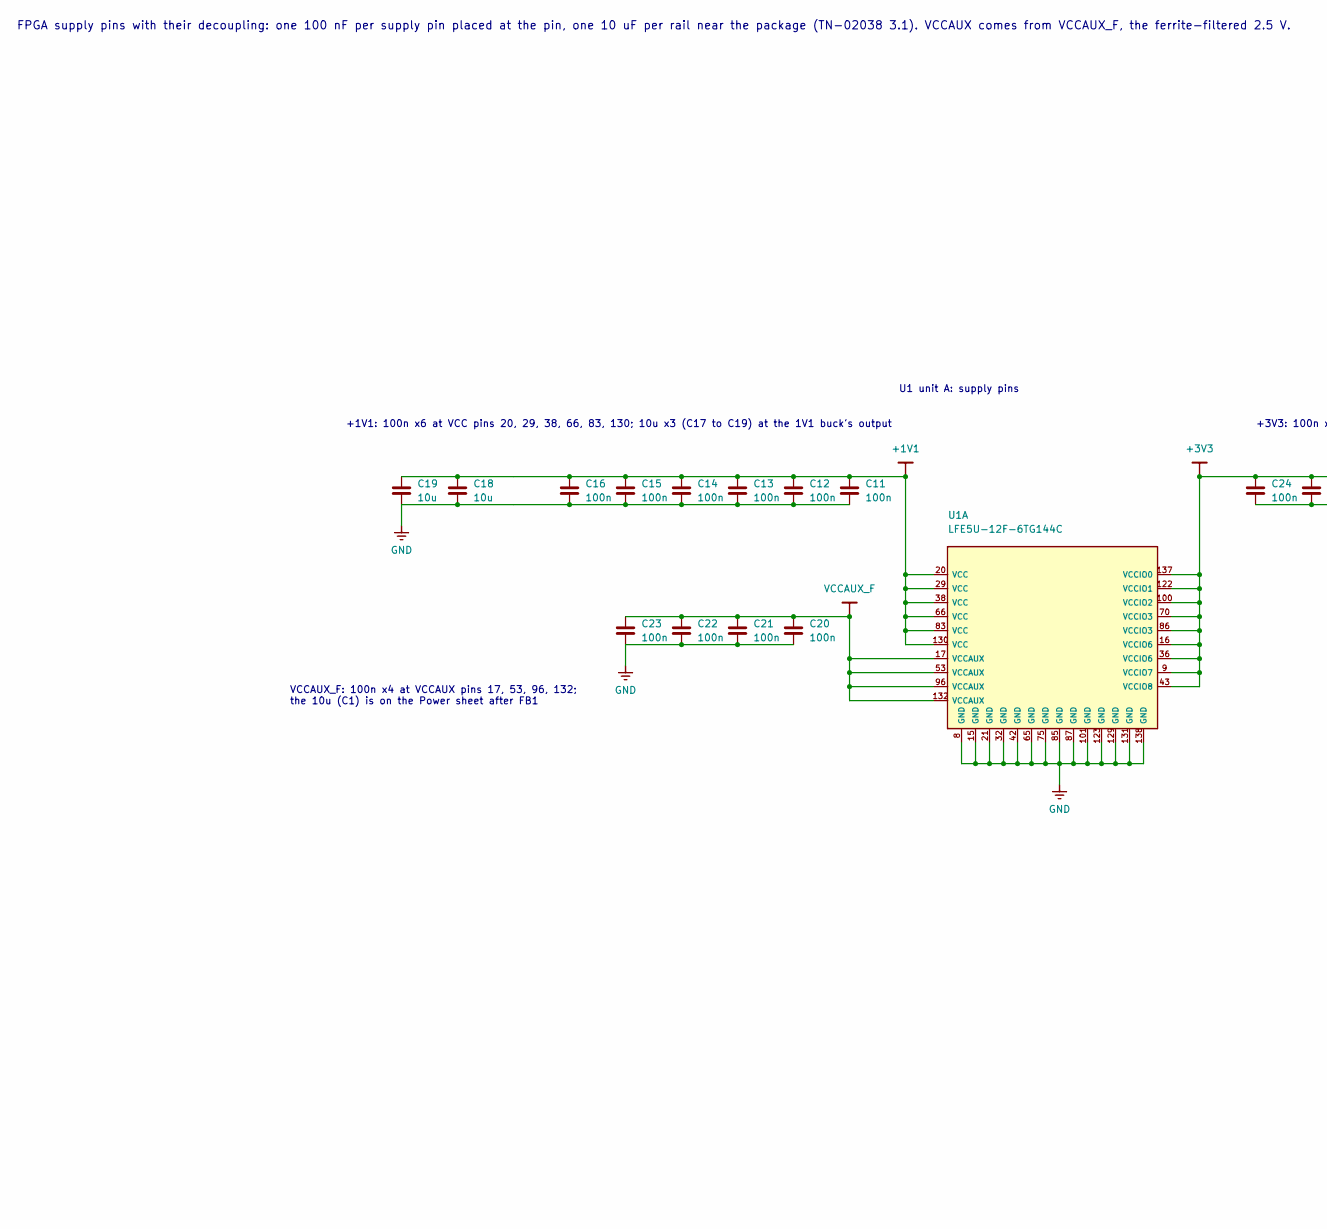
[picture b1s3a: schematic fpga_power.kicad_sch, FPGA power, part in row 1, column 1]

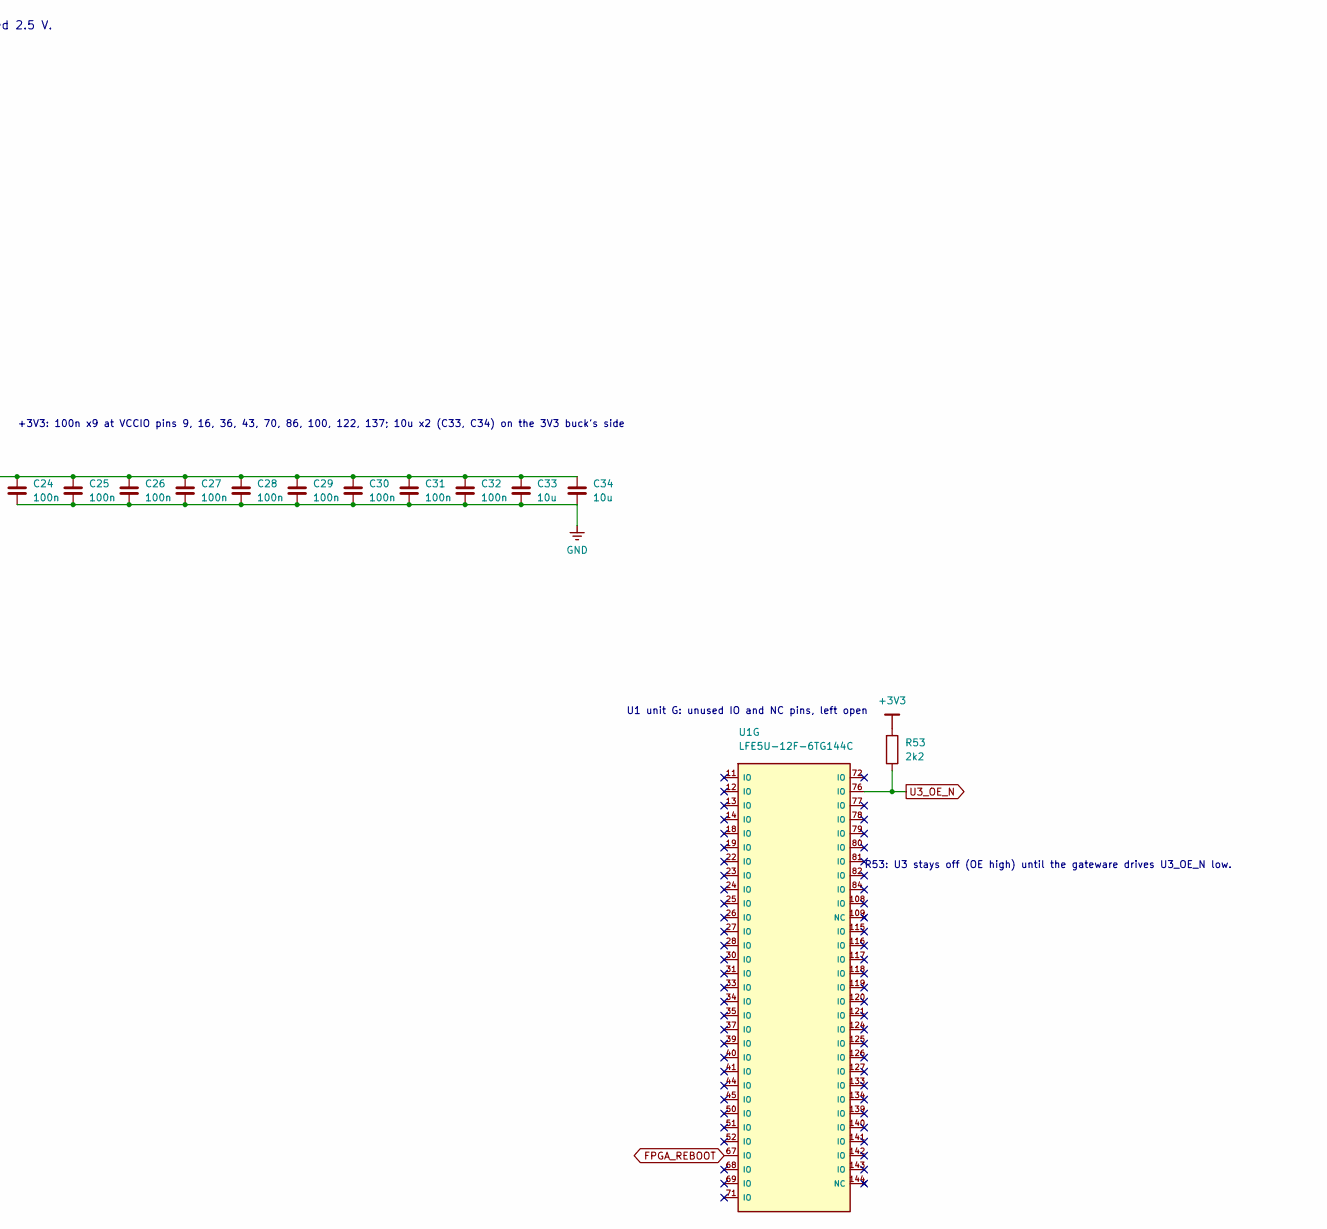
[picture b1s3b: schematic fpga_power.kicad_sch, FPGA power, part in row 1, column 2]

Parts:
C11, C12, C13, C14, C15, C16, C20, C21, C22, C23, C24, C25, C26, C27, C28, C29, C30, C31, C32: 100n; C_0603_1608Metric; MPN Samsung CL10B104KO8NNNC; LCSC C66501
C18, C19, C33, C34: 10u; C_0603_1608Metric; MPN Murata GRM188R61E106MA73D; LCSC C91606
R53: 2k2; R_0603_1608Metric; MPN Yageo RC0603FR-072K2L; LCSC C114662
U1: LFE5U-12F-6TG144C; TQFP-144_20x20mm_P0.5mm; MPN Lattice LFE5U-12F-6TG144C; LCSC C19979181

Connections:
+1V1: C11.1, C12.1, C13.1, C14.1, C15.1, C16.1, C18.1, C19.1, U1.20 (VCC), U1.29 (VCC), U1.38 (VCC), U1.66 (VCC), U1.83 (VCC), U1.130 (VCC); also elsewhere on the board
FPGA_REBOOT: U1.67 (IO); also elsewhere on the board
U3_OE_N: R53.2, U1.76 (IO); also elsewhere on the board
VCCAUX_F: C20.1, C21.1, C22.1, C23.1, U1.17 (VCCAUX), U1.53 (VCCAUX), U1.96 (VCCAUX), U1.132 (VCCAUX); also elsewhere on the board

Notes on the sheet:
FPGA supply pins with their decoupling: one 100 nF per supply pin placed at the pin, one 10 uF per rail near the package (TN-02038 3.1). VCCAUX comes from VCCAUX_F, the ferrite-filtered 2.5 V.
U1 unit A: supply pins
+1V1: 100n x6 at VCC pins 20, 29, 38, 66, 83, 130; 10u x3 (C17 to C19) at the 1V1 buck's output
VCCAUX_F: 100n x4 at VCCAUX pins 17, 53, 96, 132; the 10u (C1) is on the Power sheet after FB1
+3V3: 100n x9 at VCCIO pins 9, 16, 36, 43, 70, 86, 100, 122, 137; 10u x2 (C33, C34) on the 3V3 buck's side
U1 unit G: unused IO and NC pins, left open
R53: U3 stays off (OE high) until the gateware drives U3_OE_N low.

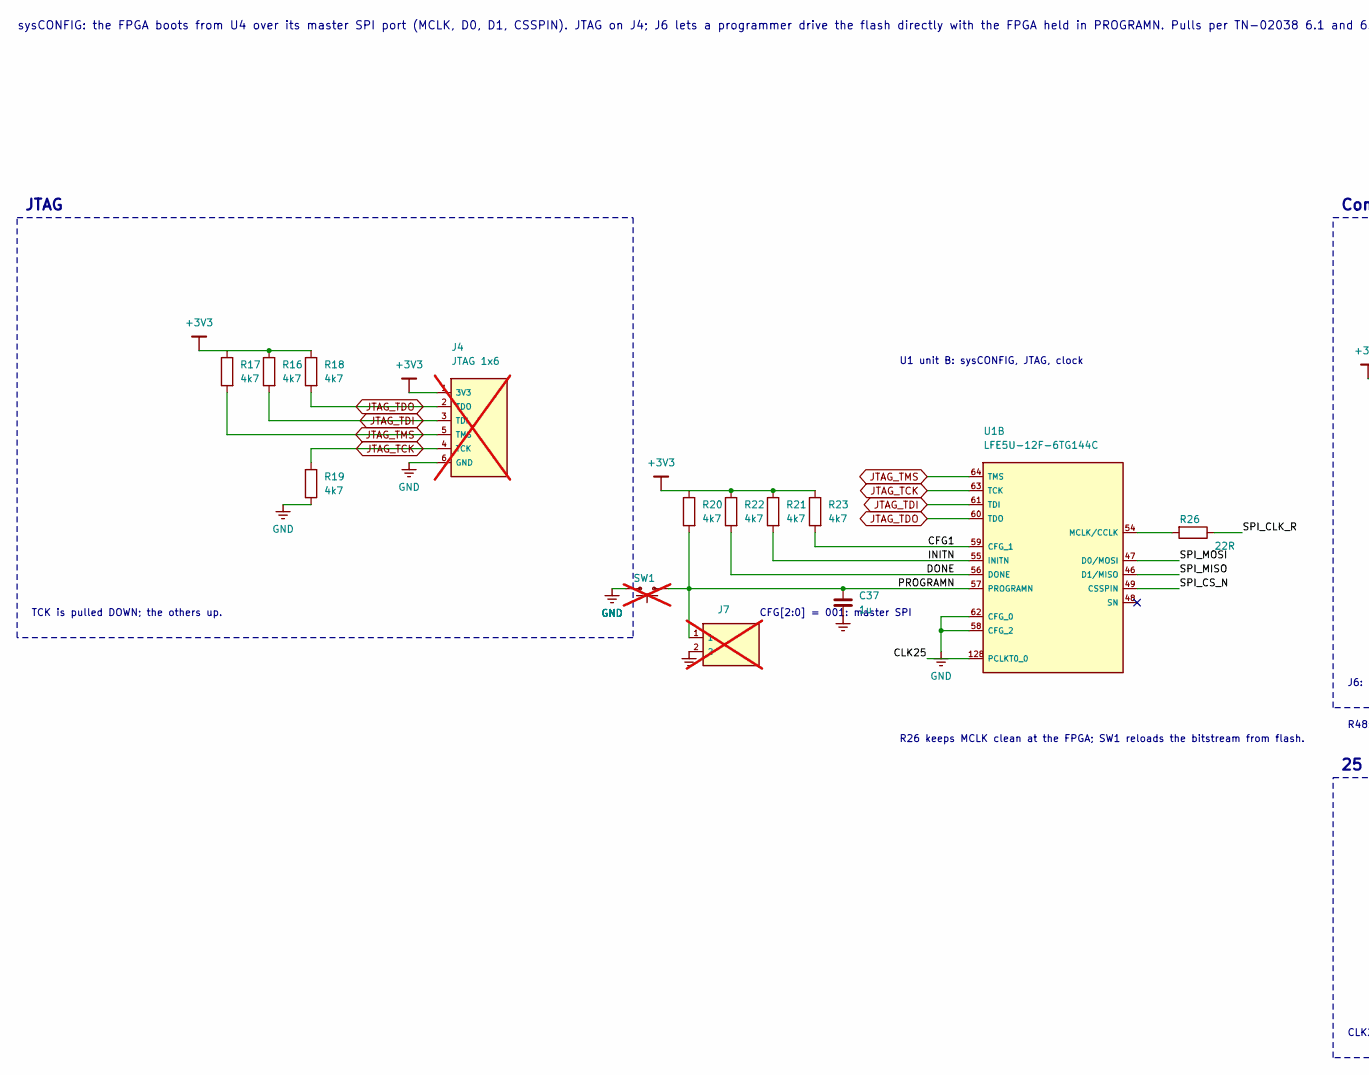
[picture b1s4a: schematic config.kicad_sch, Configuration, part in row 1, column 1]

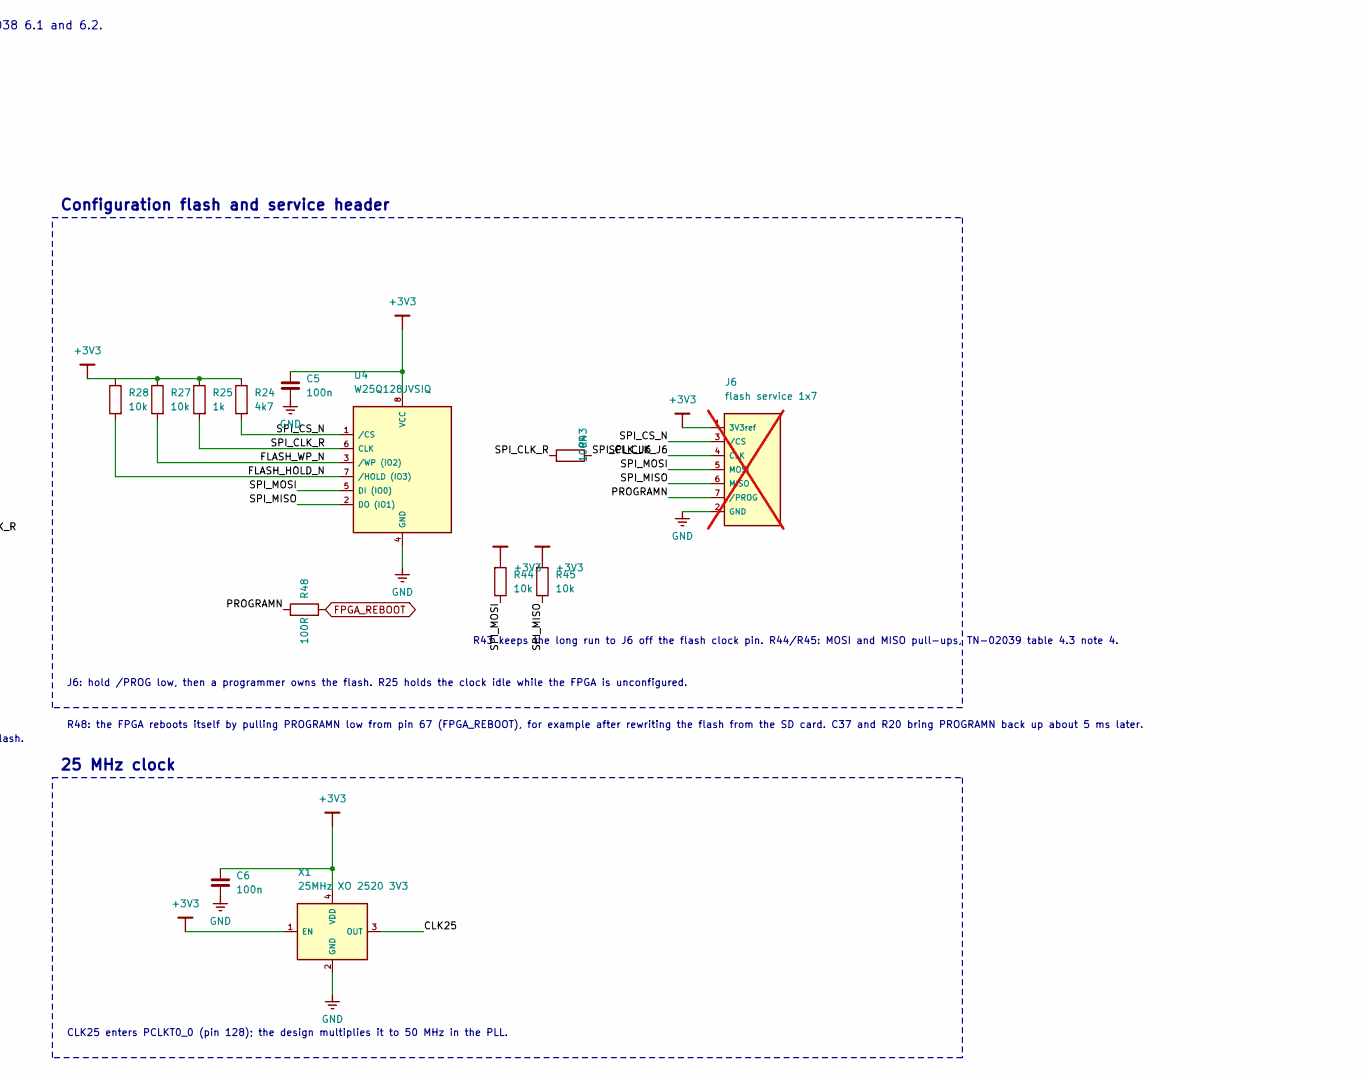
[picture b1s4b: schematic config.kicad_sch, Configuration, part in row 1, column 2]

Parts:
C5, C6: 100n; C_0603_1608Metric; MPN Samsung CL10B104KO8NNNC; LCSC C66501
C37: 1u; C_0603_1608Metric; MPN Samsung CL10B105KA8NNNC; LCSC C29936
J4: JTAG 1x6; PinHeader_1x06_P2.54mm_Vertical; LCSC C37208; not fitted
J6: flash service 1x7; PinHeader_1x07_P2.54mm_Vertical; not fitted
J7: PROGRAMN button header (optional); PinHeader_1x02_P2.54mm_Vertical; not fitted
R16, R17, R18, R19, R20, R21, R22, R23, R24: 4k7; R_0603_1608Metric; MPN Yageo RC0603FR-074K7L; LCSC C99782
R25: 1k; R_0603_1608Metric; MPN Yageo RC0603FR-071KL; LCSC C22548
R26: 22R; R_0603_1608Metric; MPN Yageo RC0603FR-0722RL; LCSC C107701
R27, R28, R44, R45: 10k; R_0603_1608Metric; MPN Yageo RC0603FR-0710KL; LCSC C98220
R43, R48: 100R; R_0603_1608Metric; MPN Yageo RC0603FR-07100RL; LCSC C105588
SW1: PROGRAMN button; SW_Push_SameSky_TS18-5; MPN Same Sky TS18-5-15-SL-260-SMT-TR; LCSC C7074292; not fitted
U1: LFE5U-12F-6TG144C; TQFP-144_20x20mm_P0.5mm; MPN Lattice LFE5U-12F-6TG144C; LCSC C19979181
U4: W25Q128JVSIQ; SOIC-8_Dual_150-208mil_P1.27mm; MPN Winbond W25Q128JVSIQ; LCSC C97521
X1: 25MHz XO 2520 3V3; Oscillator_SMD_ECS_2520MV-xxx-xx-4Pin_2.5x2.0mm; MPN ECS ECS-2520MV-250-BN-TR; LCSC C405463

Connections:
/Configuration/CFG1: R23.1, U1.59 (CFG_1)
/Configuration/CLK25: U1.128 (PCLKT0_0), X1.3 (OUT)
/Configuration/DONE: R22.1, U1.56 (DONE)
/Configuration/FLASH_HOLD_N: R28.1, U4.7 (/HOLD (IO3))
/Configuration/FLASH_WP_N: R27.1, U4.3 (/WP (IO2))
/Configuration/INITN: R21.1, U1.55 (INITN)
/Configuration/PROGRAMN: C37.1, J6.7 (/PROG), J7.1, R20.1, R48.1, SW1.1, U1.57 (PROGRAMN)
/Configuration/SPI_CLK_J6: J6.4 (CLK), R43.2
/Configuration/SPI_CLK_R: R25.1, R26.2, R43.1, U4.6 (CLK)
/Configuration/SPI_CS_N: J6.3 (/CS), R24.1, U1.49 (CSSPIN), U4.1 (/CS)
/Configuration/SPI_MISO: J6.6 (MISO), R45.2, U1.46 (D1/MISO), U4.2 (DO (IO1))
/Configuration/SPI_MOSI: J6.5 (MOSI), R44.2, U1.47 (D0/MOSI), U4.5 (DI (IO0))
FPGA_REBOOT: R48.2; also elsewhere on the board
JTAG_TCK: J4.4 (TCK), R19.1, U1.63 (TCK)
JTAG_TDI: J4.3 (TDI), R16.1, U1.61 (TDI)
JTAG_TDO: J4.2 (TDO), R18.1, U1.60 (TDO)
JTAG_TMS: J4.5 (TMS), R17.1, U1.64 (TMS)
unnamed: R26.1, U1.54 (MCLK/CCLK)

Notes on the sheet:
sysCONFIG: the FPGA boots from U4 over its master SPI port (MCLK, D0, D1, CSSPIN). JTAG on J4; J6 lets a programmer drive the flash directly with the FPGA held in PROGRAMN. Pulls per TN-02038 6.1 and 6.2.
U1 unit B: sysCONFIG, JTAG, clock
CFG[2:0] = 001: master SPI
R26 keeps MCLK clean at the FPGA; SW1 reloads the bitstream from flash.
JTAG
TCK is pulled DOWN; the others up.
Configuration flash and service header
J6: hold /PROG low, then a programmer owns the flash. R25 holds the clock idle while the FPGA is unconfigured.
25 MHz clock
CLK25 enters PCLKT0_0 (pin 128); the design multiplies it to 50 MHz in the PLL.
R43 keeps the long run to J6 off the flash clock pin. R44/R45: MOSI and MISO pull-ups, TN-02039 table 4.3 note 4.
R48: the FPGA reboots itself by pulling PROGRAMN low from pin 67 (FPGA_REBOOT), for example after rewriting the flash from the SD card. C37 and R20 bring PROGRAMN back up about 5 ms later.

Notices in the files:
fpga/hw-r2/profile-drive/profile-drive.kicad_pcb:
(c) 2026 Jorj Bauer
